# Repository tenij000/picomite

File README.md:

# picomite
pico computer that runs picomite

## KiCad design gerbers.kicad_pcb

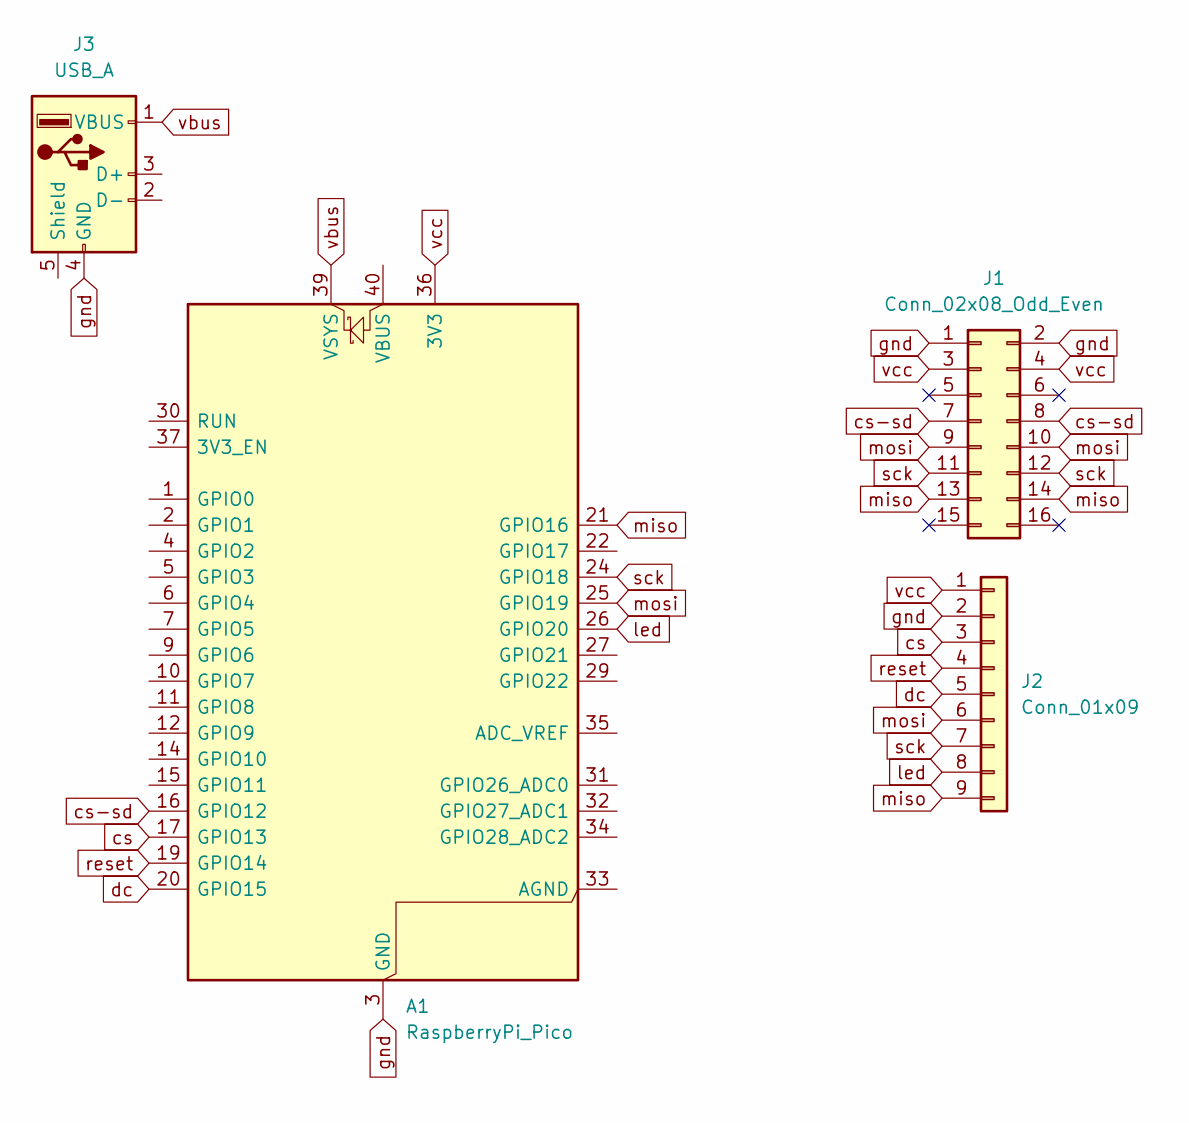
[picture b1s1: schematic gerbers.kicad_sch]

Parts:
A1: RaspberryPi_Pico; RaspberryPi_Pico_Common_Unspecified
J1: Conn_02x08_Odd_Even; PinHeader_2x08_P2.54mm_Vertical
J2: Conn_01x09; PinHeader_1x09_P2.54mm_Vertical
J3: USB_A; USB_A_Molex_67643_Horizontal

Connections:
cs: A1.17 (GPIO13), J2.3
cs-sd: A1.16 (GPIO12), J1.7, J1.8
dc: A1.20 (GPIO15), J2.5
gnd: A1.3 (GND), A1.8 (GND), A1.13 (GND), A1.18 (GND), A1.23 (GND), A1.28 (GND), A1.38 (GND), J1.1, J1.2, J2.2, J3.4 (GND)
led: A1.26 (GPIO20), J2.8
miso: A1.21 (GPIO16), J1.13, J1.14, J2.9
mosi: A1.25 (GPIO19), J1.9, J1.10, J2.6
reset: A1.19 (GPIO14), J2.4
sck: A1.24 (GPIO18), J1.11, J1.12, J2.7
vbus: A1.39 (VSYS), J3.1 (VBUS)
vcc: A1.36 (3V3), J1.3, J1.4, J2.1

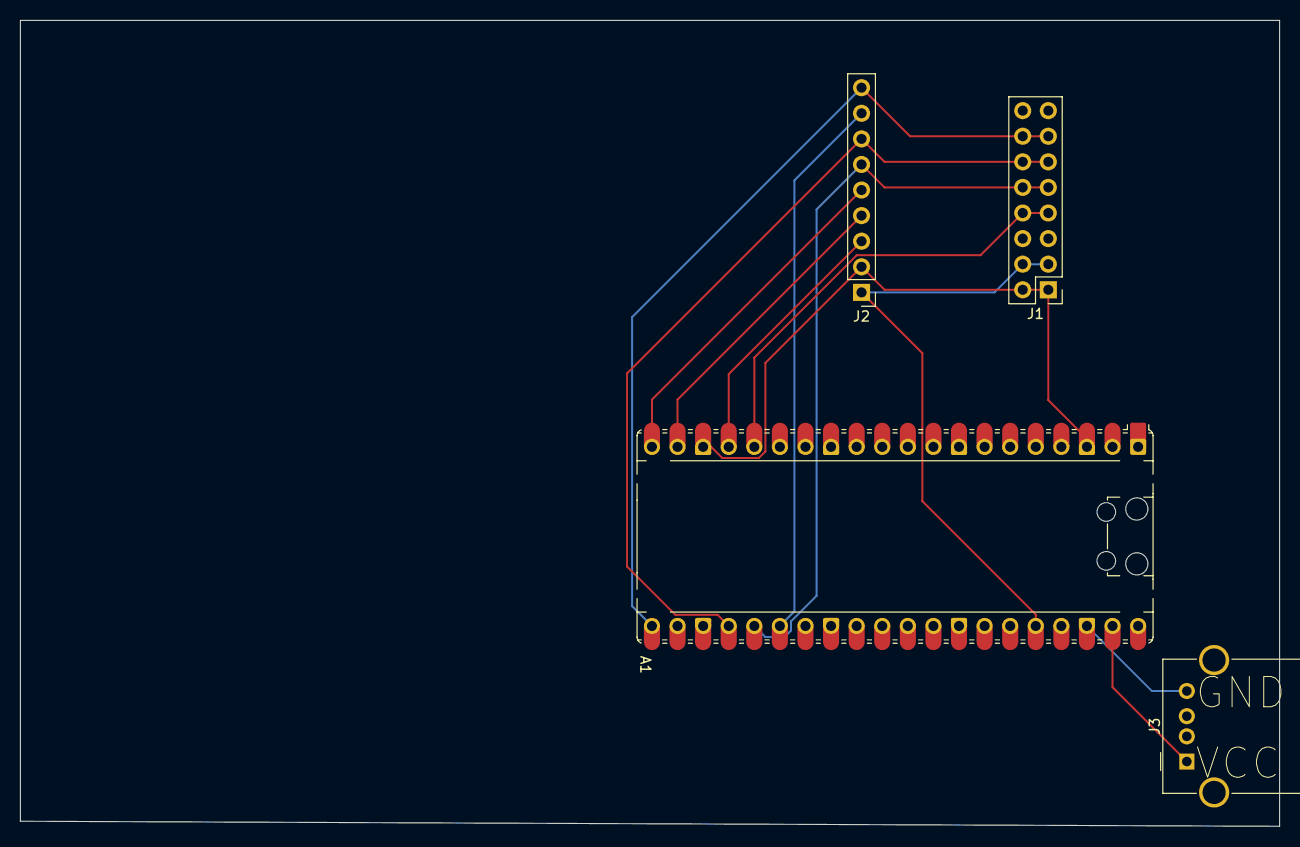
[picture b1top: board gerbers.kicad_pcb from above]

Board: 2 copper layers, 125.0 x 80.0 mm, 4 parts (0 on the bottom side), 11 nets.
